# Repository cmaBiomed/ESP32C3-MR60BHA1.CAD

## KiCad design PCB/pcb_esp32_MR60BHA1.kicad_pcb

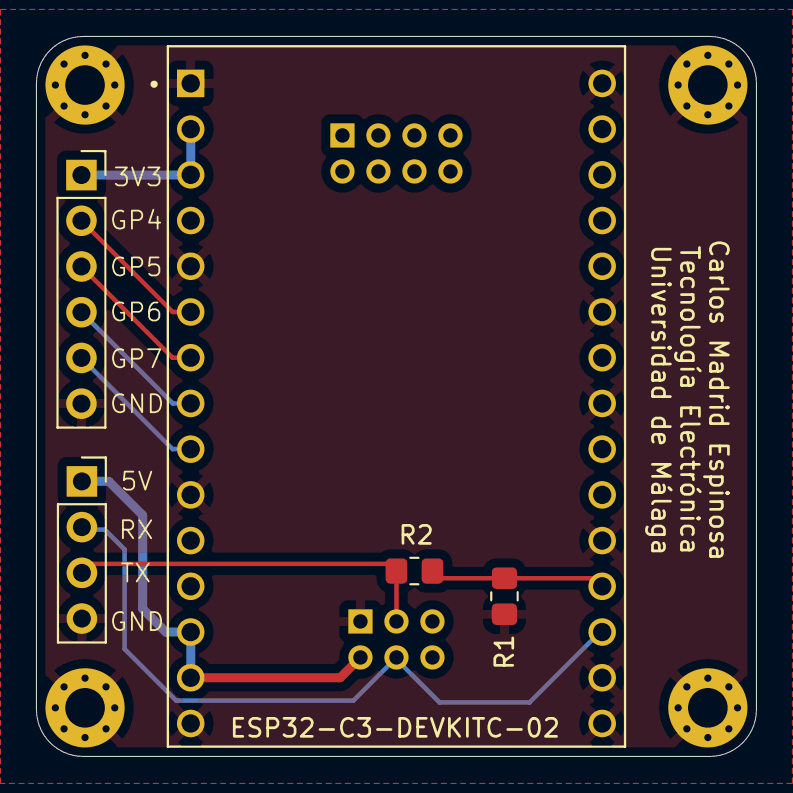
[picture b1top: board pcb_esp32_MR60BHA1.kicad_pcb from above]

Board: 2 copper layers, 40.0 x 40.0 mm, 10 parts (1 on the bottom side), 6 nets.

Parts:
H1, H2, H3, H4: MountingHole_Pad; MountingHole_2.2mm_M2_Pad_Via
J1: Conn_01x04; PinSocket_1x04_P2.54mm_Vertical
J2: Conn_01x06; PinSocket_1x06_P2.54mm_Vertical
R1: 20k; R_0805_2012Metric_Pad1.20x1.40mm_HandSolder
R2: 10k; R_0805_2012Metric_Pad1.20x1.40mm_HandSolder
U1: MR60BHA1; MR60BHA1_MALE2x3_THT
U2: ESP32-C3-DEVKITC-02; XCVR_ESP32-C3-DEVKITC-02

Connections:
+3V3: J2.1, U2.2 (3V3), U2.3 (3V3)
+5V: J1.1, U1.2 (5V), U2.13 (5V), U2.14 (5V)
/RX_ESP: R1.2, R2.1, U2.19 (GPIO18)
/RX_Sensor: J1.2, U1.4 (RX), U2.18 (GPIO19)
/Tx_Sensor: J1.3, R2.2, U1.3 (TX)
GND: H1.1, H2.1, H3.1, H4.1, J1.4, J2.6, R1.1, U1.1 (GND), U2.1 (GND), U2.5 (GND), U2.10 (GND), U2.15 (GND), U2.16 (GND), U2.17 (GND), U2.20 (GND), U2.23 (GND), U2.25 (GND), U2.30 (GND)

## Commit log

2024-06-21 Primer Commit incluyo los archovos de la PCB
2024-06-21 Envolvente y ECAD del MR60BHA1 añadidos
